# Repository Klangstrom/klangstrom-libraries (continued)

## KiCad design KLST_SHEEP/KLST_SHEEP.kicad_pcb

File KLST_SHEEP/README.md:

# KLANGSTROM / KLST_SHEEP

KLST_SHEEP is a *wolf in sheep's clothing* it is similar to KLST_TINY however comes with a stronger MCU and a screen:

- featuring *KLANGSTROM* library
- programmable in Arduino IDE via USB ( *DFUse Mode* )
- debugging + communication via *virtual USB Serial Port*

## feature list

- STM32H743 MCU with 480MHz, 864KB RAM, 2048KB Flash
- WM8731 audio codec with 2× audio DAC + 2× audio ADC ( 16/24BIT )
- 1× LINE OUT ( stereo )
- 1× LINE IN ( stereo )
- 1× HEADPHONE + MIC ( mono )
- 2× ADC ( 12BIT, opt 6 extra channels )
- 2× DAC ( 12BIT )
- 2× UART ( serial )
- 16× GPIO
- 1× USB Host
- 1× USB Device ( + Power Supply )
- 1× I2C 
- 1× SPI 
- 2× rotary encoders with push buttons
- 16× programmable LEDs with PWM + 1× power LED
- 1× SD card reader
- 1× JTAG/SWD interface + serial debug ( 14-pin )
- programmer + reset + boot flash buttons
- 4× Mounting Holes

## technical details

### timers

| TIMER | FUNCTION                         |
|-------|----------------------------------|
| TIM1  | ENCODER_00                       |
| TIM2  | ENCODER_01                       |
| TIM3  | LED_PWM                          |
| TIM4  | LED_PWM                          |
| TIM5  | (UNUSED)                         |
| TIM6  | BEAT_CALLBACK                    |
| TIM7  | TIMER_SERVO                      |
| TIM8  | LED_PWM                          |
| TIM9  | (nA)                             |
| TIM10 | (nA)                             |
| TIM11 | (nA)                             |
| TIM12 | TIMER_TONE                       |
| TIM13 | LED_PWM                          |
| TIM14 | LED_PWM                          |
| TIM15 | LED_PWM                          |
| TIM16 | LED_PWM                          |
| TIM17 | BUTTON_PRG_IT                    |

#### encoders

timers `TIM1` + `TIM2` are used to handle encoder events.

| FUNCTION          | TIMER:CHANNEL |
|-------------------|---------------|
| ENCODER_00_A+B    | TIM1          |
| ENCODER_00_BUTTON | TIM1:CH3      |
| ENCODER_01_A+B    | TIM2          |
| ENCODER_01_BUTTON | TIM2:CH4      |

#### timers for LEDs with PWM

timers `TIM3` + `TIM4` + `TIM8` + `TIM13` + `TIM14` + `TIM15` + `TIM16` are used for PWM signal generation for LEDs.

| TIMER | CHANNEL |
|-------|---------|
| TIM3  | CH1–4   |
| TIM4  | CH1–4   |
| TIM8  | CH1–4   |
| TIM13 | CH1     |
| TIM14 | CH1     |
| TIM15 | CH1     |
| TIM16 | CH1     |

LEDs are mapped to the following timers:

| LED    | PIN   | TIMER:CHANNEL |
|--------|-------|---------------|
| LED_00 | PB8   | TIM16:CH1     |
| LED_01 | PB5   | TIM3:CH2      |
| LED_02 | PB4   | TIM3:CH1      |
| LED_03 | PC9   | TIM8:CH4      |
| LED_04 | PC8   | TIM8:CH3      |
| LED_05 | PC7*  | TIM8:CH2      |
| LED_06 | PC6*  | TIM8:CH1      |
| LED_07 | PD15  | TIM4:CH4      |
| LED_08 | PD14  | TIM4:CH3      |
| LED_09 | PD13  | TIM4:CH2      |
| LED_10 | PD12  | TIM4:CH1      |
| LED_11 | PB1   | TIM3:CH4      |
| LED_12 | PB0   | TIM3:CH3      |
| LED_13 | PA7   | TIM14:CH1     |
| LED_14 | PA6*  | TIM13:CH1     |
| LED_15 | PA2   | TIM15:CH1     |

#### timer-based PWM alternative PINs

most GPIO pins do not have PWM capabilities. however, the following peripheral pins can be reconfigured to produce PWM signals ( at the expanse of other peripherals ):

| FUNCTION       | PIN  | TIMER:CHANNEL        |
|----------------|------|----------------------|
| DAC_01         | PA5  | TIM2:CH1 / TIM8:CH1N |
| USB_DEVICE-    | PA11 | TIM1:CH4             |
| SPI_DISPLAY_CS | PA15 | TIM2:CH1             |
| I2C_USR_SCL    | PB6  | TIM4:CH1             |
| I2C_USR_SDA    | PB7  | TIM4:CH2             |
| GPIO_10        | PE9  | TIM1:CH1             |
| SPI_USR_CS     | PE11 | TIM1:CH2             |
| SPI_USR_MISO   | PE13 | TIM1:CH3             |
| SPI_USR_MOSI   | PE14 | TIM1:CH4             |

### I2C

| FUNCTION   | PERIPHERAL |
|------------|------------|
| AUDIOCODEC | I2C1       |
| I2C_USR    | I2C2       |

### SPI

| FUNCTION | PERIPHERAL |
|----------|------------|
| SD-CARD  | SPI2       |
| DISPLAY  | SPI3       |
| SPI_USR  | SPI6       |

### UART

| FUNCTION     | PERIPHERAL |
|--------------|------------|
| SERIAL_00    | UART7      |
| SERIAL_01    | UART8      |
| SERIAL_DEBUG | USART2     |

## PIN assignment

| PIN  | LABEL                       |
|------|-----------------------------|
| PC4  | ADC_00                      |
| PC5  | ADC_01                      |
| PB6  | AUDIOCODEC_I2C_SCL          |
| PB7  | AUDIOCODEC_I2C_SDA          |
| PE4  | AUDIOCODEC_SAI1_FS_A        |
| PE2  | AUDIOCODEC_SAI1_MCLK_A      |
| PE5  | AUDIOCODEC_SAI1_SCK_A       |
| PE6  | AUDIOCODEC_SAI1_SD_A        |
| PE3  | AUDIOCODEC_SAI1_SD_B        |
| PB9  | BUTTON_PRG                  |
| PA4  | DAC_00                      |
| PA5  | DAC_01                      |
| PA0  | ENCODER_00_A                |
| PA1  | ENCODER_00_B                |
| PA3  | ENCODER_00_BUTTON           |
| PA8  | ENCODER_01_A                |
| PA9  | ENCODER_01_B                |
| PA10 | ENCODER_01_BUTTON           |
| PD7  | GPIO_00                     |
| PD4  | GPIO_01                     |
| PD3  | GPIO_02                     |
| PD2  | GPIO_03                     |
| PD11 | GPIO_04                     |
| PD10 | GPIO_05                     |
| PD9  | GPIO_06                     |
| PD8  | GPIO_07                     |
| PE15 | GPIO_08                     |
| PE10 | GPIO_09                     |
| PE9  | GPIO_10                     |
| PB2  | GPIO_11                     |
| PC0  | GPIO_12                     |
| PC15 | GPIO_13                     |
| PC14 | GPIO_14                     |
| PC13 | GPIO_15                     |
| PB10 | I2C_USR_SCL                 |
| PB11 | I2C_USR_SDA                 |
| PB8  | LED_00                      |
| PB5  | LED_01                      |
| PB4  | LED_02                      |
| PC9  | LED_03                      |
| PC8  | LED_04                      |
| PC7  | LED_05                      |
| PC6  | LED_06                      |
| PD15 | LED_07                      |
| PD14 | LED_08                      |
| PD13 | LED_09                      |
| PD12 | LED_10                      |
| PB1  | LED_11                      |
| PB0  | LED_12                      |
| PA7  | LED_13                      |
| PA6  | LED_14                      |
| PA2  | LED_15                      |
| PB12 | SDCARD_CS                   |
| PC2  | SDCARD_MISO                 |
| PC3  | SDCARD_MOSI                 |
| PB13 | SDCARD_SCK                  |
| PC1  | SDCARD_CARD_DETECT          |
| PE7  | SERIAL_00_RX                |
| PE8  | SERIAL_00_TX                |
| PE0  | SERIAL_01_RX                |
| PE1  | SERIAL_01_TX                |
| PD6  | SERIAL_DEBUG_RX             |
| PD5  | SERIAL_DEBUG_TX             |
| PA15 | SPI_DISPLAY_CS              |
| PC11 | SPI_DISPLAY_MISO            |
| PC12 | SPI_DISPLAY_MOSI            |
| PD0  | SPI_DISPLAY_REGISTER_SELECT |
| PD1  | SPI_DISPLAY_RESET           |
| PC10 | SPI_DISPLAY_SCK             |
| PE11 | SPI_USR_CS                  |
| PE13 | SPI_USR_MISO                |
| PE14 | SPI_USR_MOSI                |
| PE12 | SPI_USR_SCK                 |
| PA14 | SWD_SWCLK                   |
| PA13 | SWD_SWDIO                   |
| PB3  | SWD_SWO                     |
| PA11 | USB_DEVICE-                 |
| PA12 | USB_DEVICE+                 |
| PB14 | USB_HOST-                   |
| PB15 | USB_HOST+                   |

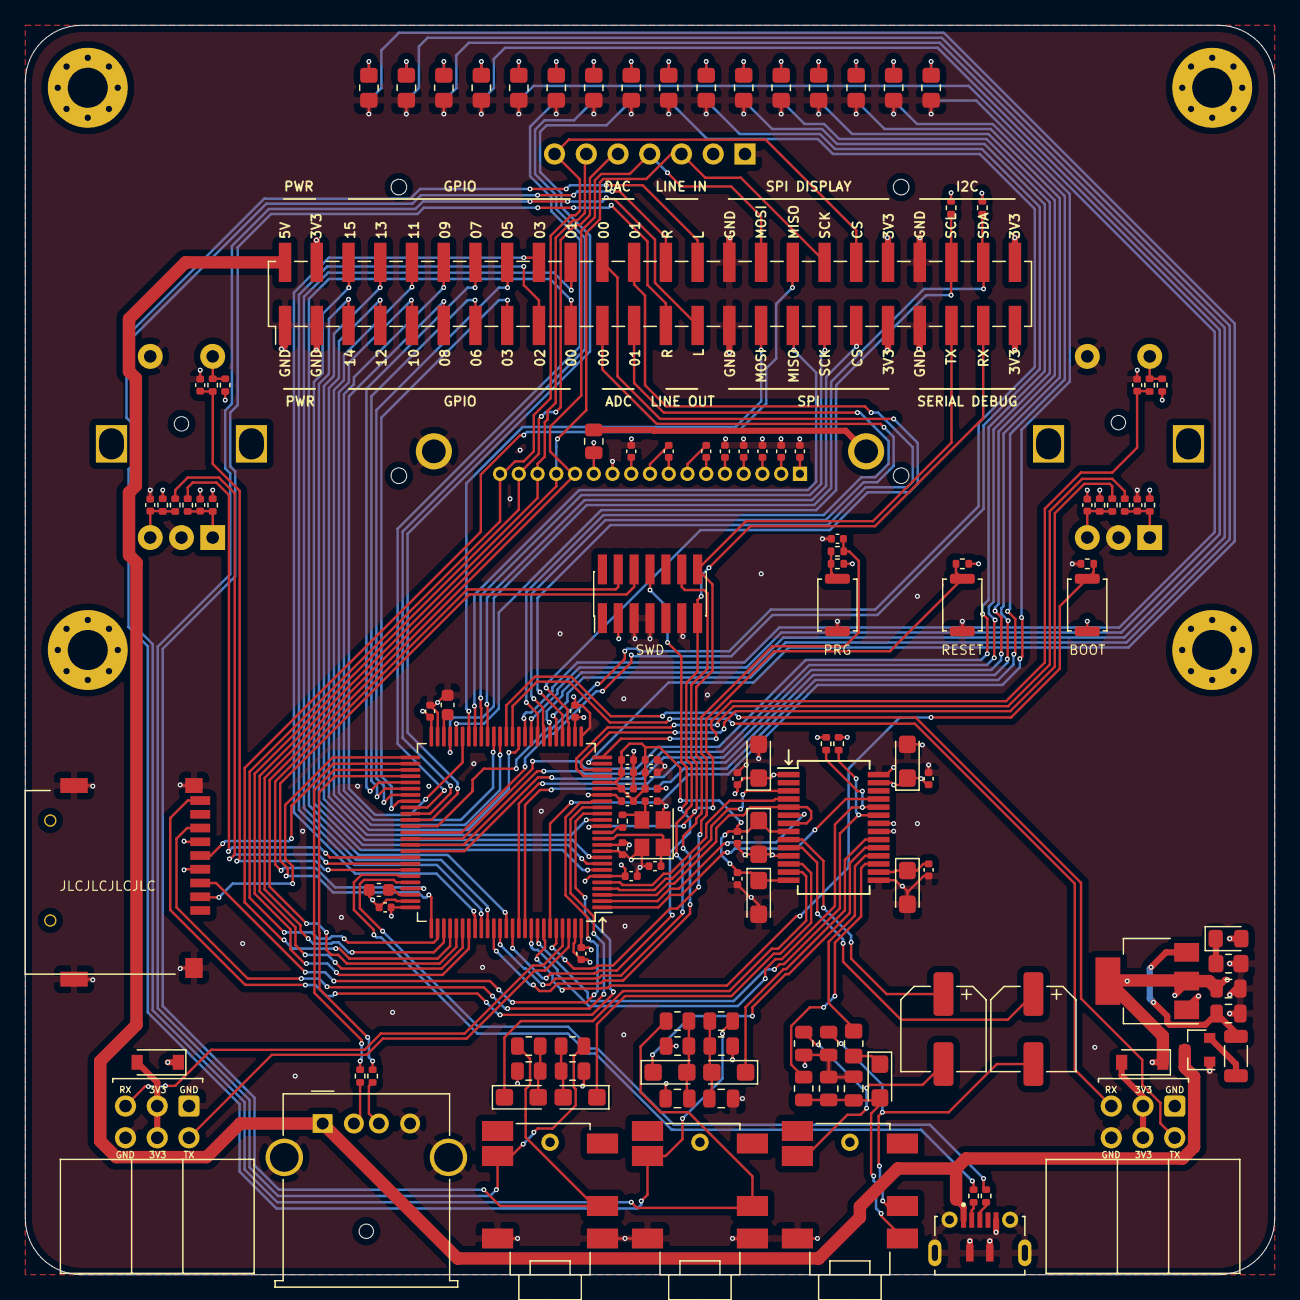
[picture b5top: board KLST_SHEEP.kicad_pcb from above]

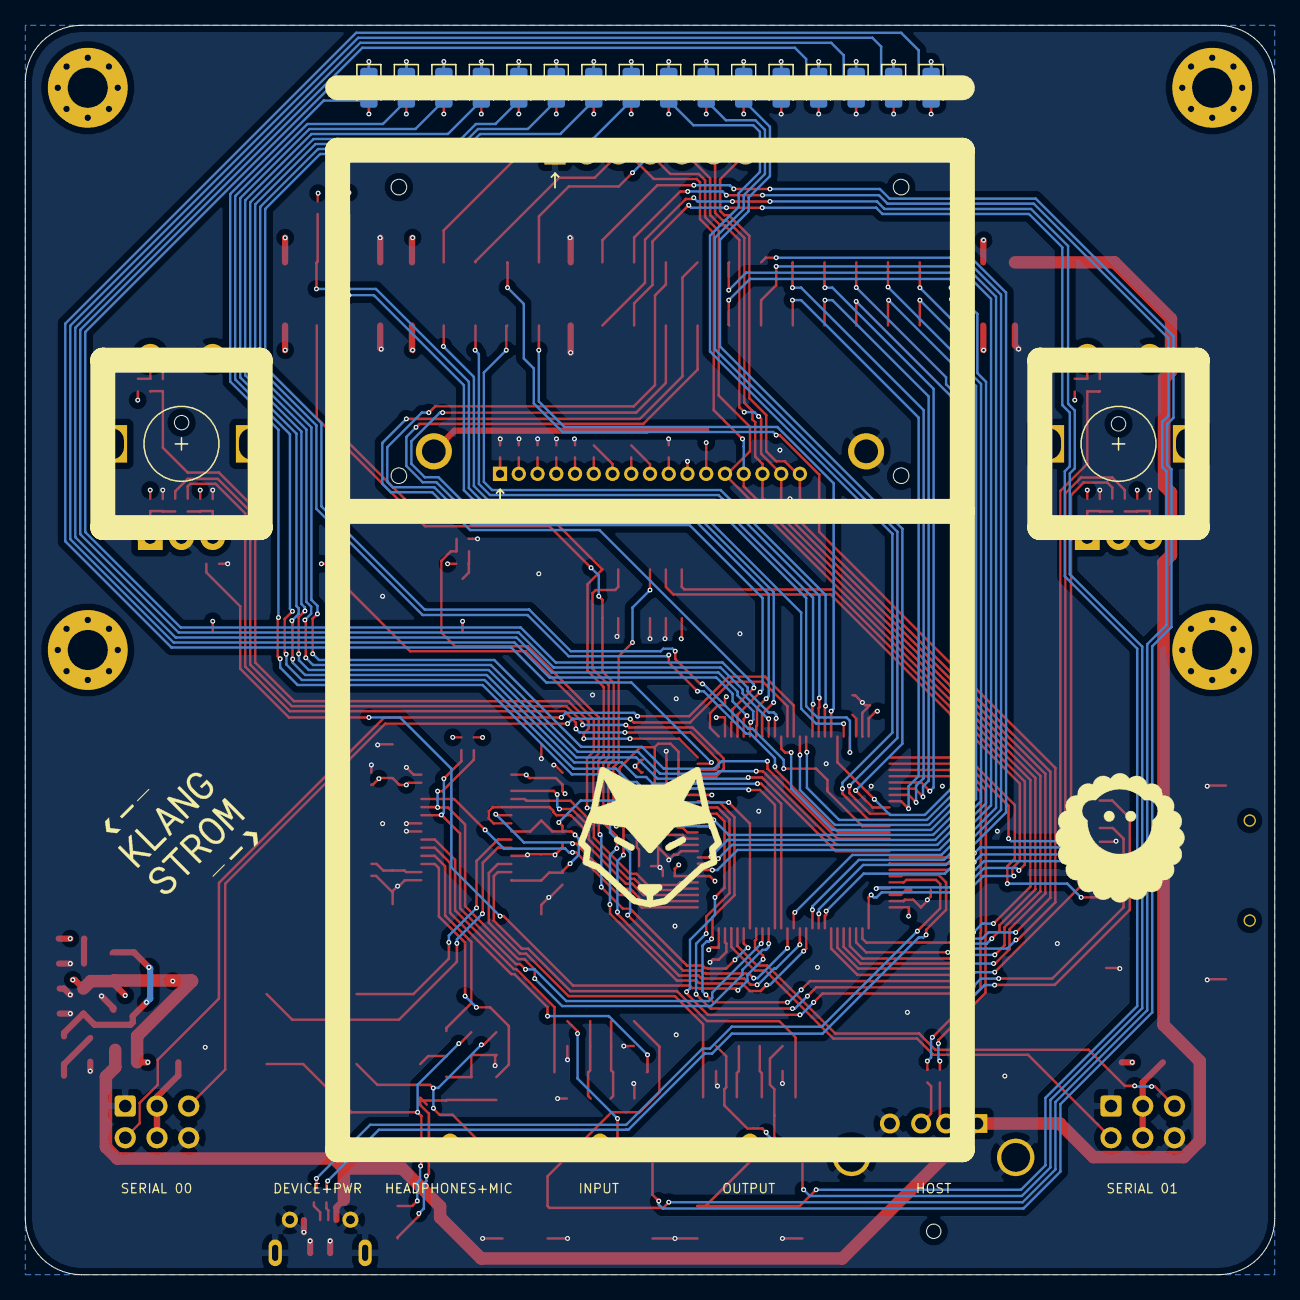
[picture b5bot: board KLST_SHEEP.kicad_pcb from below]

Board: 4 copper layers, 100.0 x 100.0 mm, 159 parts (23 on the bottom side), 155 nets.

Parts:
C1, C2: 12pF; C_0402_1005Metric
C3, C5, C12, C13, C15, C18, C20: 1uF; C_0402_1005Metric
C4, C6, C7, C8, C9, C14, C16, C21, C22, C23, C24, C25, C32, C39, C41, C43, C45, C47, C48, C49, C50, C51, C52, C53: 100nF; C_0402_1005Metric
C10, C11: 10uF; C_0805_2012Metric
C17, C26: 2.2uF; C_0603_1608Metric
C19: 10nF; C_0402_1005Metric
C27, C28: 220uF; CP_Elec_6.3x5.4
C29, C33, C35, C37, C38: 1uF; CP_EIA-3216-18_Kemet-A
C30, C34, C36: 220pF; C_0805_2012Metric
C31, C40, C42, C44, C46: 10uF; CP_EIA-3216-18_Kemet-A
D1, D2, D3, D4, D5, D6, D7, D8, D9, D10, D11, D12, D13, D14, D15, D16, D17: LED; LED_0805_2012Metric_Pad1.15x1.40mm_HandSolder
D18, D19: D_Schottky; D_SOD-123
DS1: NHD-C12832A1Z-FSW-FBW-3V3; Newhaven_Display-NHD-C12832A1Z-FSW-FBW-3V3
FB1: 600Ω@100MHz; L_1206_3216Metric
H1, H2, H3, H4: MountingHole; MountingHole_3.2mm_M3_Pad_Via
J1: Micro_SD_Card_Card_Detect_SPI; microSD_SOFNG_TF-015
J2: PERIPHERALS; PinHeader_2x24_P2.54mm_Vertical_SMD
J3: USB_A; USB_A_Molex_67643_Horizontal
J5: USB_B_Micro; SHOUHAN_MICROXNJ
J8: GMT028-05_V1.1; PinSocket_1x07_P2.54mm_Vertical
J9: ARM_JTAG_SWD(STDC14); PinHeader_2x07_P1.27mm_Vertical_SMD
J10: HEADPHONES+MIC; Korean_Hroparts_Elec_PJ-316A-6A
J11: LINE_IN; Korean_Hroparts_Elec_PJ-316A-6A
J12: LINE_OUT; Korean_Hroparts_Elec_PJ-316A-6A
J13: UART_00; IDC-Header_2x03_P2.54mm_Horizontal
J15: UART_01; IDC-Header_2x03_P2.54mm_Horizontal
L1: 39nH; L_0402_1005Metric
Q1: AO3401A; SOT-23
R1, R2, R3, R4: 22R; R_0402_1005Metric
R5, R6, R7, R8, R9, R10, R11, R12, R13, R16, R17, R18, R19, R20, R21, R22, R23: 1K; R_0805_2012Metric_Pad1.20x1.40mm_HandSolder
R14: 10R; R_0402_1005Metric
R15, R24, R41, R43, R44, R45, R46, R47, R49, R50, R51, R52, R55: 10K; R_0402_1005Metric
R25: 30R; R_0805_2012Metric
R26, R27, R32, R38, R40: 47K; R_0805_2012Metric
R28: 680R; R_0805_2012Metric
R29, R30, R53, R54: 2.2K; R_0402_1005Metric
R31: 330R; R_0805_2012Metric_Pad1.20x1.40mm_HandSolder
R33, R34, R35, R36: 5.6K; R_0805_2012Metric
R37, R39: 100R; R_0805_2012Metric
R42, R48, R56: 1K; R_0402_1005Metric
SW1: BUTTON_BOOT_FLASH; SW_Push_SPST_NO_Alps_SKRK
SW2: BUTTON_RESET; SW_Push_SPST_NO_Alps_SKRK
SW3, SW4: ENCODER; RotaryEncoder_Alps_EC12E-Switch_Vertical_H20mm
SW5: BUTTON; SW_Push_SPST_NO_Alps_SKRK
U1: STM32H743VITx; LQFP-100_14x14mm_P0.5mm
U2: AMS1117-3.3; SOT-223-3_TabPin2
U3: WM8731SEDS; SSOP-28_5.3x10.2mm_P0.65mm
X1: KLST_SHEEP--graphics; KLST--icon
X2: KLST_SHEEP--icon
X3: KLST_SHEEP--wolf
Y1: 16MHz; Crystal_SMD_3225-4Pin_3.2x2.5mm

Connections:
+3.3VA: C13.1, C14.1, C15.1, C16.1, C18.1, C19.1, C39.2, C40.1, C41.2, C42.1, L1.2, U1.20, U1.21, U3.8, U3.14
+3V3: C11.1, C20.1, C21.1, C22.1, C23.1, C24.1, C25.1, C43.2, C44.1, C45.2, C46.1, D9.2, D18.1, D19.1, DS1.12, J1.4, J2.4, J2.39, J2.40, J2.47, J2.48, J8.2, J9.3, L1.1, R15.2, R25.2, R29.1, R30.1, R41.2, R43.1, R44.1, R47.2, R49.1, R50.1, R53.1, R54.1, R55.2, SW1.2, U1.6, U1.11, U1.27, U1.50, U1.75, U1.100, U2.2, U3.1, U3.27
+5V: J2.2, J3.1, J5.1, Q1.3
/ADCDAT: U1.2, U3.6
/ADCLRC: U1.3, U3.5, U3.7
/ADC_00: J2.21, U1.32
/ADC_01: J2.23, U1.33
/AUDIOCODEC_I2C_SCL: R29.2, U1.92, U3.24
/AUDIOCODEC_I2C_SDA: R30.2, U1.93, U3.23
/AUDIOCODEC_I2S_CK: U1.4, U3.3
/AUDIOCODEC_I2S_MCK: U1.1, U3.25
/AUDIOCODEC_I2S_SDO: U1.5, U3.4
/BOOT_FLASH: R24.2, SW1.1, U1.94
/BUTTON_PRG: C53.1, R56.1, U1.96
/DAC_00: J2.22, U1.28
/DAC_01: J2.24, U1.29
/ENCODER_00_A: R45.2, U1.22
/ENCODER_00_B: R46.1, U1.23
/ENCODER_00_BUTTON: C47.1, R42.1, U1.25
/ENCODER_01_A: R51.2, U1.67
/ENCODER_01_B: R52.1, U1.68
/ENCODER_01_BUTTON: C50.1, R48.1, U1.69
/GPIO_00: J2.19, U1.88
/GPIO_01: J2.20, U1.85
/GPIO_02: J2.17, U1.84
/GPIO_03: J2.18, U1.83
/GPIO_04: J2.15, U1.58
/GPIO_05: J2.16, U1.57
/GPIO_06: J2.13, U1.56
/GPIO_07: J2.14, U1.55
/GPIO_08: J2.11, U1.45
/GPIO_09: J2.12, U1.40
/GPIO_10: J2.9, U1.39
/GPIO_11: J2.10, U1.36
/GPIO_12: J2.7, U1.15
/GPIO_13: J2.8, U1.9
/GPIO_14: J2.5, U1.8
/GPIO_15: J2.6, U1.7
/I2C_USR_SCL: J2.44, R54.2, U1.46
/I2C_USR_SDA: J2.46, R53.2, U1.47
/LED_00: D17.2, U1.95
/LED_01: D16.2, U1.91
/LED_02: D15.2, U1.90
/LED_03: D14.2, U1.66
/LED_04: D13.2, U1.65
/LED_05: D12.2, U1.64
/LED_06: D11.2, U1.63
/LED_07: D10.2, U1.62
/LED_08: D8.2, U1.61
/LED_09: D7.2, U1.60
/LED_10: D6.2, U1.59
/LED_11: D5.2, U1.35
/LED_12: D4.2, U1.34
/LED_13: D3.2, U1.31
/LED_14: D2.2, U1.30
/LED_15: D1.2, U1.24
/LINE_IN_LEFT: J2.28, J11.T, R33.2
/LINE_IN_RIGHT: J2.26, J11.R1, R35.2
/LINE_OUT_LEFT: J2.27, J12.T, R37.2
/LINE_OUT_RIGHT: J2.25, J12.R1, R39.2
/RCC_OSC_IN: C1.2, U1.12, Y1.1
/RCC_OSC_OUT: R14.1, U1.13
/SDCARD_CARD_DETECT: J1.9, U1.16
/SDCARD_CS: J1.2, U1.51
/SDCARD_MISO: J1.7, U1.17
/SDCARD_MOSI: J1.3, U1.18
/SDCARD_SCK: J1.5, U1.52
/SERIAL_00_RX: J13.5, U1.37
/SERIAL_00_TX: J13.2, U1.38
/SERIAL_01_RX: J15.5, U1.97
/SERIAL_01_TX: J15.2, U1.98
/SERIAL_DEBUG_RX: J2.45, J9.13, U1.87
/SERIAL_DEBUG_TX: J2.43, J9.14, U1.86
/SPI_DISPLAY_CS: DS1.17, J2.38, J8.7, U1.77
/SPI_DISPLAY_MISO: J2.34, U1.79
/SPI_DISPLAY_MOSI: DS1.13, J2.32, J8.4, U1.80
/SPI_DISPLAY_REGISTER_SELECT: DS1.15, J8.6, U1.81
/SPI_DISPLAY_RESET: DS1.16, J8.5, U1.82
/SPI_DISPLAY_SCK: DS1.14, J2.36, J8.3, U1.78
/SPI_USR_CS: J2.37, U1.41
/SPI_USR_MISO: J2.33, U1.43
/SPI_USR_MOSI: J2.31, U1.44
/SPI_USR_SCK: J2.35, U1.42
/SWD_NRST: J9.12, R15.1, SW2.2, U1.14
/SWD_SWCLK: J9.6, U1.76
/SWD_SWDIO: J9.4, U1.72
/SWD_SWO: J9.8, U1.89
/USB_DEVICE+: R3.1, U1.71
/USB_DEVICE-: R1.1, U1.70
/USB_HOST+: R2.1, U1.54
/USB_HOST-: R4.1, U1.53
/VCAP1: C17.1, U1.48
/VCAP2: C26.1, U1.73
/audio_codec_WM8731/HEADPHONE_LEFT: C27.2, J10.T, R26.1
/audio_codec_WM8731/HEADPHONE_RIGHT: C28.2, J10.R1, R27.1
/audio_codec_WM8731/MIC_IN: C29.2, C30.2, J10.S, R28.1, R32.1
/audio_codec_WM8731/SIGNAL_HEADPHONE_LEFT: C27.1, U3.9
/audio_codec_WM8731/SIGNAL_HEADPHONE_RIGHT: C28.1, U3.10
/audio_codec_WM8731/SIGNAL_IN_LEFT: C33.1, U3.20
/audio_codec_WM8731/SIGNAL_IN_RIGHT: C35.1, U3.19
/audio_codec_WM8731/SIGNAL_MIC_BIAS: R28.2, U3.17
/audio_codec_WM8731/SIGNAL_MIC_IN: R31.2, U3.18
/audio_codec_WM8731/SIGNAL_OUT_LEFT: C37.1, U3.12
/audio_codec_WM8731/SIGNAL_OUT_RIGHT: C38.1, U3.13
GND: C1.1, C2.2, C4.2, C6.2, C7.2, C8.2, C9.2, C10.2, C11.2, C12.2, C13.2, C14.2, C15.2, C16.2, C17.2, C18.2, C19.2, C20.2, C21.2, C22.2, C23.2, C24.2, C25.2, C26.2, C30.1, C31.2, C32.2, C34.1, C36.1, C39.1, C40.2, C41.1, C42.2, C43.1, C44.2, C45.1, C46.2, C47.2, C48.2, C49.2, C50.2, C51.2, C52.2, C53.2, DS1.11, DS1.K, J1.6, J1.10, J2.1, J2.3, J2.29, J2.30, J2.41, J2.42, J3.4, J3.5, J5.5, J5.S, J8.1, J9.5, J9.7, J9.11, J10.R2, J11.R2, J11.S, J12.R2, J12.S, J13.1, J13.6, J15.1, J15.6, Q1.1, R5.1, R6.1, R7.1, R8.1, R9.1, R10.1, R11.1, R12.1, R13.1, R16.1, R17.1, R18.1, R19.1, R20.1, R21.1, R22.1, R23.1, R24.1, R26.2, R27.2, R32.2, R34.2, R36.2, R38.2, R40.2, SW2.1, SW3.C, SW3.S2, SW4.C, SW4.S2, SW5.2, U1.10, U1.19, U1.26, U1.49, U1.74, U1.99, U2.1, U3.11, U3.15, U3.21, U3.22, U3.28, Y1.2, Y1.4
unnamed: C2.1, R14.2, Y1.3
unnamed: C3.1, DS1.8
unnamed: C3.2, DS1.9
unnamed: C4.1, DS1.1
unnamed: C5.1, DS1.7
unnamed: C5.2, DS1.6
unnamed: C6.1, DS1.2
unnamed: C7.1, DS1.3
unnamed: C8.1, DS1.4
unnamed: C9.1, DS1.5
unnamed: C10.1, FB1.1, U2.3
unnamed: C12.1, DS1.10
unnamed: C29.1, R31.1
unnamed: C31.1, C32.1, U3.16
unnamed: C33.2, C34.2, R33.1, R34.1
unnamed: C35.2, C36.2, R35.1, R36.1
unnamed: C37.2, R37.1, R38.1
unnamed: C38.2, R39.1, R40.1
unnamed: C48.1, R44.2, R45.1, SW3.A
unnamed: C49.1, R43.2, R46.2, SW3.B
unnamed: C51.1, R50.2, R51.1, SW4.A
unnamed: C52.1, R49.2, R52.2, SW4.B
unnamed: D1.1, R5.2
unnamed: D2.1, R6.2
unnamed: D3.1, R7.2
unnamed: D4.1, R8.2
unnamed: D5.1, R9.2
unnamed: D6.1, R10.2
unnamed: D7.1, R11.2
unnamed: D8.1, R12.2
unnamed: D9.1, R13.2
unnamed: D10.1, R16.2
unnamed: D11.1, R17.2
unnamed: D12.1, R18.2
unnamed: D13.1, R19.2
unnamed: D14.1, R20.2
unnamed: D15.1, R21.2
unnamed: D16.1, R22.2
unnamed: D17.1, R23.2
unnamed: D18.2, J13.3, J13.4
unnamed: D19.2, J15.3, J15.4
unnamed: DS1.A, R25.1
unnamed: FB1.2, Q1.2
unnamed: J3.2, R4.2
unnamed: J3.3, R2.2
unnamed: J5.2, R1.2
unnamed: J5.3, R3.2
unnamed: R41.1, R42.2, SW3.S1
unnamed: R47.1, R48.2, SW4.S1
unnamed: R55.1, R56.2, SW5.1

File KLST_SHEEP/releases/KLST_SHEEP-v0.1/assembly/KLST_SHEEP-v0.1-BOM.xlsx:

Comment | Designator | Footprint | JLCPCB Part #
Micro_SD_Card_Card_Detect_SPI | J1 | Connector_Card:microSD_SOFNG_TF-015 | C113206
STM32H743VITx | U1 | Package_QFP:LQFP-100_14x14mm_P0.5mm | C114409
BUTTON_RESET | SW2 | Button_Switch_SMD:SW_Push_SPST_NO_Alps_SKRK | C115357
BUTTON_BOOT_FLASH | SW1 | Button_Switch_SMD:SW_Push_SPST_NO_Alps_SKRK | C115357
BUTTON | SW5 | Button_Switch_SMD:SW_Push_SPST_NO_Alps_SKRK | C115357
1K | R56 | Resistor_SMD:R_0402_1005Metric | C11702
1K | R42 | Resistor_SMD:R_0402_1005Metric | C11702
1K | R48 | Resistor_SMD:R_0402_1005Metric | C11702
HEADPHONES+MIC | J10 | KLST_SHEEP:Korean_Hroparts_Elec_PJ-316A-6A | C128987
LINE_IN | J11 | KLST_SHEEP:Korean_Hroparts_Elec_PJ-316A-6A | C128987
LINE_OUT | J12 | KLST_SHEEP:Korean_Hroparts_Elec_PJ-316A-6A | C128987
16MHz | Y1 | Crystal:Crystal_SMD_3225-4Pin_3.2x2.5mm | C13738
UART_01 | J15 | Connector_IDC:IDC-Header_2x03_P2.54mm_Horizontal | C146629
UART_00 | J13 | Connector_IDC:IDC-Header_2x03_P2.54mm_Horizontal | C146629
AO3401A | Q1 | Package_TO_SOT_SMD:SOT-23 | C15127
10nF | C19 | Capacitor_SMD:C_0402_1005Metric | C15195
100nF | C14 | Capacitor_SMD:C_0402_1005Metric | C1525
100nF | C21 | Capacitor_SMD:C_0402_1005Metric | C1525
100nF | C22 | Capacitor_SMD:C_0402_1005Metric | C1525
100nF | C23 | Capacitor_SMD:C_0402_1005Metric | C1525
100nF | C24 | Capacitor_SMD:C_0402_1005Metric | C1525
100nF | C25 | Capacitor_SMD:C_0402_1005Metric | C1525
100nF | C16 | Capacitor_SMD:C_0402_1005Metric | C1525
100nF | C4 | Capacitor_SMD:C_0402_1005Metric | C1525
100nF | C6 | Capacitor_SMD:C_0402_1005Metric | C1525
100nF | C7 | Capacitor_SMD:C_0402_1005Metric | C1525
100nF | C8 | Capacitor_SMD:C_0402_1005Metric | C1525
100nF | C9 | Capacitor_SMD:C_0402_1005Metric | C1525
100nF | C32 | Capacitor_SMD:C_0402_1005Metric | C1525
100nF | C43 | Capacitor_SMD:C_0402_1005Metric | C1525
100nF | C45 | Capacitor_SMD:C_0402_1005Metric | C1525
100nF | C39 | Capacitor_SMD:C_0402_1005Metric | C1525
100nF | C41 | Capacitor_SMD:C_0402_1005Metric | C1525
100nF | C53 | Capacitor_SMD:C_0402_1005Metric | C1525
100nF | C48 | Capacitor_SMD:C_0402_1005Metric | C1525
100nF | C49 | Capacitor_SMD:C_0402_1005Metric | C1525
100nF | C47 | Capacitor_SMD:C_0402_1005Metric | C1525
100nF | C51 | Capacitor_SMD:C_0402_1005Metric | C1525
100nF | C52 | Capacitor_SMD:C_0402_1005Metric | C1525
100nF | C50 | Capacitor_SMD:C_0402_1005Metric | C1525
12pF | C1 | Capacitor_SMD:C_0402_1005Metric | C1547
12pF | C2 | Capacitor_SMD:C_0402_1005Metric | C1547
10uF | C10 | Capacitor_SMD:C_0805_2012Metric | C15850
10uF | C11 | Capacitor_SMD:C_0805_2012Metric | C15850
100R | R37 | Resistor_SMD:R_0805_2012Metric | C17408
100R | R39 | Resistor_SMD:R_0805_2012Metric | C17408
1K | R13 | Resistor_SMD:R_0805_2012Metric_Pad1.20x1.40mm_HandSolder | C17513
1K | R6 | Resistor_SMD:R_0805_2012Metric_Pad1.20x1.40mm_HandSolder | C17513
1K | R7 | Resistor_SMD:R_0805_2012Metric_Pad1.20x1.40mm_HandSolder | C17513
1K | R5 | Resistor_SMD:R_0805_2012Metric_Pad1.20x1.40mm_HandSolder | C17513
1K | R8 | Resistor_SMD:R_0805_2012Metric_Pad1.20x1.40mm_HandSolder | C17513
1K | R9 | Resistor_SMD:R_0805_2012Metric_Pad1.20x1.40mm_HandSolder | C17513
1K | R10 | Resistor_SMD:R_0805_2012Metric_Pad1.20x1.40mm_HandSolder | C17513
1K | R11 | Resistor_SMD:R_0805_2012Metric_Pad1.20x1.40mm_HandSolder | C17513
1K | R12 | Resistor_SMD:R_0805_2012Metric_Pad1.20x1.40mm_HandSolder | C17513
1K | R17 | Resistor_SMD:R_0805_2012Metric_Pad1.20x1.40mm_HandSolder | C17513
1K | R18 | Resistor_SMD:R_0805_2012Metric_Pad1.20x1.40mm_HandSolder | C17513
1K | R16 | Resistor_SMD:R_0805_2012Metric_Pad1.20x1.40mm_HandSolder | C17513
1K | R19 | Resistor_SMD:R_0805_2012Metric_Pad1.20x1.40mm_HandSolder | C17513
1K | R20 | Resistor_SMD:R_0805_2012Metric_Pad1.20x1.40mm_HandSolder | C17513
1K | R21 | Resistor_SMD:R_0805_2012Metric_Pad1.20x1.40mm_HandSolder | C17513
1K | R22 | Resistor_SMD:R_0805_2012Metric_Pad1.20x1.40mm_HandSolder | C17513
1K | R23 | Resistor_SMD:R_0805_2012Metric_Pad1.20x1.40mm_HandSolder | C17513
330R | R31 | Resistor_SMD:R_0805_2012Metric_Pad1.20x1.40mm_HandSolder | C17630
30R | R25 | Resistor_SMD:R_0805_2012Metric | C17634
47K | R26 | Resistor_SMD:R_0805_2012Metric | C17713
47K | R27 | Resistor_SMD:R_0805_2012Metric | C17713
47K | R38 | Resistor_SMD:R_0805_2012Metric | C17713
47K | R40 | Resistor_SMD:R_0805_2012Metric | C17713
47K | R32 | Resistor_SMD:R_0805_2012Metric | C17713
680R | R28 | Resistor_SMD:R_0805_2012Metric | C17798
2.2uF | C26 | Capacitor_SMD:C_0603_1608Metric | C23630
2.2uF | C17 | Capacitor_SMD:C_0603_1608Metric | C23630
10R | R14 | Resistor_SMD:R_0402_1005Metric | C25077
22R | R2 | Resistor_SMD:R_0402_1005Metric | C25092
22R | R4 | Resistor_SMD:R_0402_1005Metric | C25092
22R | R1 | Resistor_SMD:R_0402_1005Metric | C25092
22R | R3 | Resistor_SMD:R_0402_1005Metric | C25092
10K | R15 | Resistor_SMD:R_0402_1005Metric | C25744
10K | R24 | Resistor_SMD:R_0402_1005Metric | C25744
10K | R55 | Resistor_SMD:R_0402_1005Metric | C25744
10K | R45 | Resistor_SMD:R_0402_1005Metric | C25744
10K | R46 | Resistor_SMD:R_0402_1005Metric | C25744
10K | R43 | Resistor_SMD:R_0402_1005Metric | C25744
10K | R44 | Resistor_SMD:R_0402_1005Metric | C25744
10K | R41 | Resistor_SMD:R_0402_1005Metric | C25744
10K | R51 | Resistor_SMD:R_0402_1005Metric | C25744
10K | R52 | Resistor_SMD:R_0402_1005Metric | C25744
10K | R49 | Resistor_SMD:R_0402_1005Metric | C25744
10K | R50 | Resistor_SMD:R_0402_1005Metric | C25744
10K | R47 | Resistor_SMD:R_0402_1005Metric | C25744
2.2K | R53 | Resistor_SMD:R_0402_1005Metric | C25879
2.2K | R54 | Resistor_SMD:R_0402_1005Metric | C25879
2.2K | R30 | Resistor_SMD:R_0402_1005Metric | C25879
2.2K | R29 | Resistor_SMD:R_0402_1005Metric | C25879
39nH | L1 | Inductor_SMD:L_0402_1005Metric | C26443
220uF | C27 | Capacitor_SMD:CP_Elec_6.3x5.4 | C3345
220uF | C28 | Capacitor_SMD:CP_Elec_6.3x5.4 | C3345
LED | D9 | LED_SMD:LED_0805_2012Metric_Pad1.15x1.40mm_HandSolder | C34499
USB_B_Micro | J5 | KLST_SHEEP:SHOUHAN_MICROXNJ | C404969
5.6K | R33 | Resistor_SMD:R_0805_2012Metric | C4382
5.6K | R34 | Resistor_SMD:R_0805_2012Metric | C4382
5.6K | R35 | Resistor_SMD:R_0805_2012Metric | C4382
5.6K | R36 | Resistor_SMD:R_0805_2012Metric | C4382
USB_A | J3 | Connector_USB:USB_A_Molex_67643_Horizontal | C456018
1uF | C13 | Capacitor_SMD:C_0402_1005Metric | C52923
1uF | C20 | Capacitor_SMD:C_0402_1005Metric | C52923
1uF | C18 | Capacitor_SMD:C_0402_1005Metric | C52923
1uF | C15 | Capacitor_SMD:C_0402_1005Metric | C52923
1uF | C3 | Capacitor_SMD:C_0402_1005Metric | C52923
1uF | C5 | Capacitor_SMD:C_0402_1005Metric | C52923
1uF | C12 | Capacitor_SMD:C_0402_1005Metric | C52923
220pF | C34 | Capacitor_SMD:C_0805_2012Metric | C53172
220pF | C36 | Capacitor_SMD:C_0805_2012Metric | C53172
220pF | C30 | Capacitor_SMD:C_0805_2012Metric | C53172
AMS1117-3.3 | U2 | Package_TO_SOT_SMD:SOT-223-3_TabPin2 | C6186
10uF | C31 | Capacitor_Tantalum_SMD:CP_EIA-3216-18_Kemet-A | C7171
10uF | C44 | Capacitor_Tantalum_SMD:CP_EIA-3216-18_Kemet-A | C7171
10uF | C46 | Capacitor_Tantalum_SMD:CP_EIA-3216-18_Kemet-A | C7171
10uF | C40 | Capacitor_Tantalum_SMD:CP_EIA-3216-18_Kemet-A | C7171
10uF | C42 | Capacitor_Tantalum_SMD:CP_EIA-3216-18_Kemet-A | C7171
1uF | C33 | Capacitor_Tantalum_SMD:CP_EIA-3216-18_Kemet-A | C7175
1uF | C35 | Capacitor_Tantalum_SMD:CP_EIA-3216-18_Kemet-A | C7175
1uF | C37 | Capacitor_Tantalum_SMD:CP_EIA-3216-18_Kemet-A | C7175
1uF | C38 | Capacitor_Tantalum_SMD:CP_EIA-3216-18_Kemet-A | C7175
1uF | C29 | Capacitor_Tantalum_SMD:CP_EIA-3216-18_Kemet-A | C7175
600Ω@100MHz | FB1 | Inductor_SMD:L_1206_3216Metric | C73732
D_Schottky | D18 | Diode_SMD:D_SOD-123 | C8598
D_Schottky | D19 | Diode_SMD:D_SOD-123 | C8598

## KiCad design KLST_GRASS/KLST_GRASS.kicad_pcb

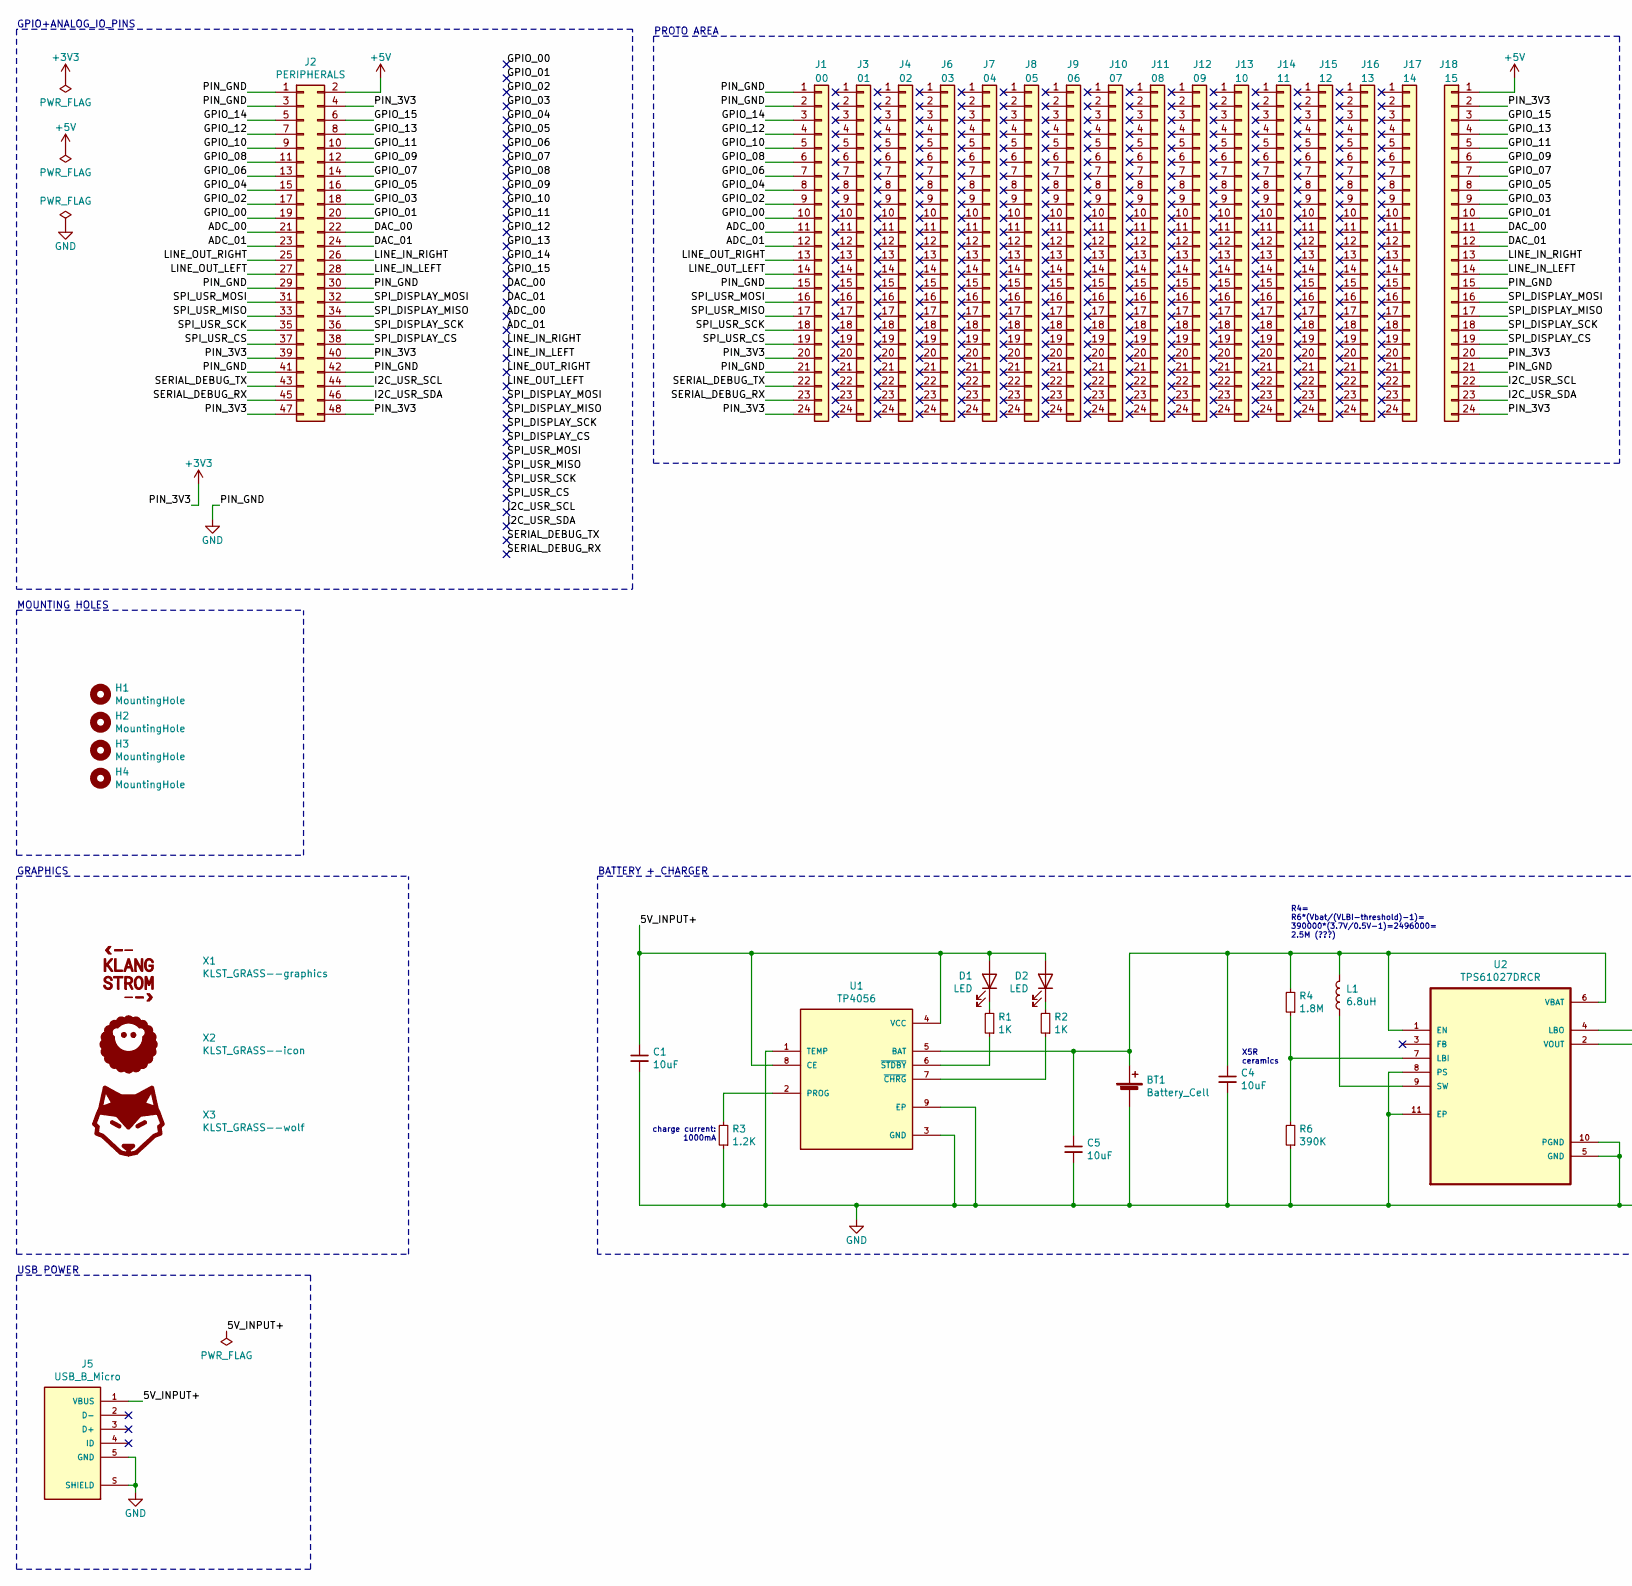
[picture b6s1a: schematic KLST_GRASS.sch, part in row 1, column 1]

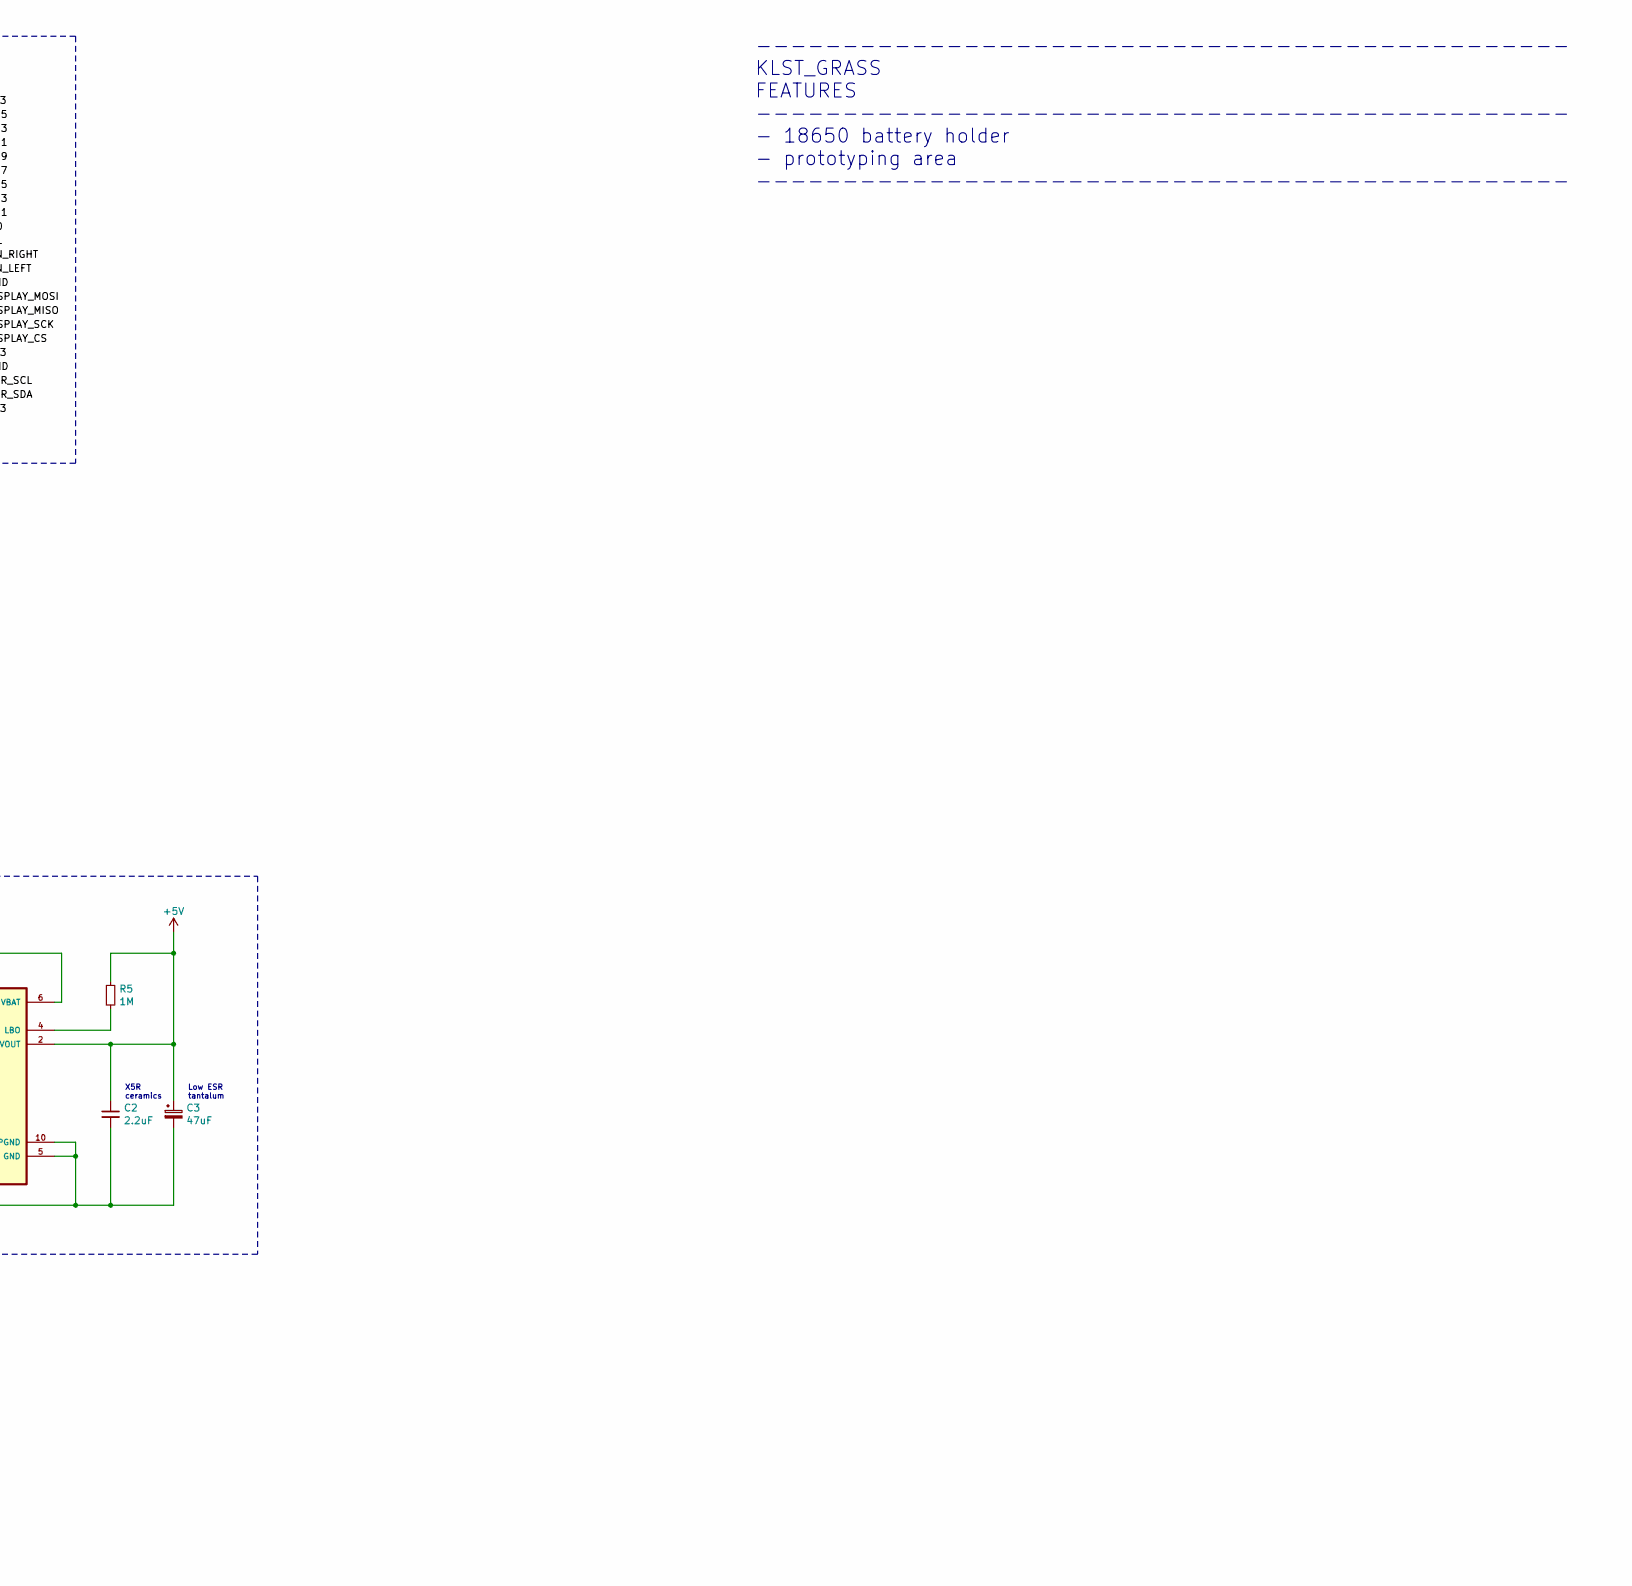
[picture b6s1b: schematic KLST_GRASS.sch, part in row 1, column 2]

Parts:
BT1: Battery_Cell; Keystone Electronics - PC Battery Clip #54
C1, C4, C5: 10uF; C_0603_1608Metric_Pad1.08x0.95mm_HandSolder; MFR.Part # CL10A106MA8NRNC; JLCPCB Part # C96446
C2: 2.2uF; C_0603_1608Metric_Pad1.08x0.95mm_HandSolder; MFR.Part # CL10A225KO8NNNC; JLCPCB Part # C23630
C3: 47uF; CP_EIA-3216-18_Kemet-A_Pad1.58x1.35mm_HandSolder; MFR.Part # TC212A476K006A; JLCPCB Part # C112111
D1, D2: LED; LED_0805_2012Metric_Pad1.15x1.40mm_HandSolder; MFR.Part # C34499; JLCPCB Part # C34499
H1, H2, H3, H4: MountingHole; MountingHole_3.2mm_M3_Pad_Via; MFR.Part # DNF; JLCPCB Part # DNF
J1: 00; PinHeader_1x24_P2.54mm_Vertical
J2: PERIPHERALS; PinHeader_2x24_P2.54mm_Vertical; MFR.Part # DNF; JLCPCB Part # DNF
J3: 01; PinHeader_1x24_P2.54mm_Vertical
J4: 02; PinHeader_1x24_P2.54mm_Vertical
J5: USB_B_Micro; SHOUHAN_MICROXNJ; MFR.Part # MicroXNJ; JLCPCB Part # C404969
J6: 03; PinHeader_1x24_P2.54mm_Vertical
J7: 04; PinHeader_1x24_P2.54mm_Vertical
J8: 05; PinHeader_1x24_P2.54mm_Vertical
J9: 06; PinHeader_1x24_P2.54mm_Vertical
J10: 07; PinHeader_1x24_P2.54mm_Vertical
J11: 08; PinHeader_1x24_P2.54mm_Vertical
J12: 09; PinHeader_1x24_P2.54mm_Vertical
J13: 10; PinHeader_1x24_P2.54mm_Vertical
J14: 11; PinHeader_1x24_P2.54mm_Vertical
J15: 12; PinHeader_1x24_P2.54mm_Vertical
J16: 13; PinHeader_1x24_P2.54mm_Vertical
J17: 14; PinHeader_1x24_P2.54mm_Vertical
J18: 15; PinHeader_1x24_P2.54mm_Vertical
L1: 6.8uH; L_Bourns-SRN4018; MFR.Part # PRS4018-6R8MT; JLCPCB Part # C105667
R1, R2: 1K; R_0805_2012Metric_Pad1.20x1.40mm_HandSolder; MFR.Part # 0805W8F1001T5E; JLCPCB Part # C17513
R3: 1.2K; R_0805_2012Metric_Pad1.20x1.40mm_HandSolder; MFR.Part # 0805W8F1201T5E; JLCPCB Part # C17379
R4: 1.8M; R_0805_2012Metric_Pad1.20x1.40mm_HandSolder; MFR.Part # 0805W8F1804T5E; JLCPCB Part # C17399
R5: 1M; R_0805_2012Metric_Pad1.20x1.40mm_HandSolder; MFR.Part # 0805W8F1004T5E; JLCPCB Part # C17514
R6: 390K; R_0805_2012Metric_Pad1.20x1.40mm_HandSolder; MFR.Part # 0805W8F3903T5E; JLCPCB Part # C17656
U1: TP4056; SOP127P600X175-9N; MFR.Part # TP4056-42-ESOP8; JLCPCB Part # C16581
U2: TPS61027DRCR; MFR.Part # TPS61027DRCR; JLCPCB Part # C80258
X1: KLST_GRASS--graphics; KLST--icon; MFR.Part # DNF; JLCPCB Part # DNF
X2: KLST_GRASS--icon; MFR.Part # DNF; JLCPCB Part # DNF
X3: KLST_GRASS--wolf; MFR.Part # DNF; JLCPCB Part # DNF

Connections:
+3V3: J1.20, J1.24, J2.4, J2.39, J2.40, J2.47, J2.48, J18.2, J18.20, J18.24
+5V: C2.1, C3.1, J2.2, J18.1, R5.1, U2.2 (VOUT)
/5V_INPUT+: C1.1, D1.2 (A), D2.2 (A), J5.1 (VBUS), U1.4 (VCC), U1.8 (CE)
/ADC_00: J1.11, J2.21
/ADC_01: J1.12, J2.23
/DAC_00: J2.22, J18.11
/DAC_01: J2.24, J18.12
/GPIO_00: J1.10, J2.19
/GPIO_01: J2.20, J18.10
/GPIO_02: J1.9, J2.17
/GPIO_03: J2.18, J18.9
/GPIO_04: J1.8, J2.15
/GPIO_05: J2.16, J18.8
/GPIO_06: J1.7, J2.13
/GPIO_07: J2.14, J18.7
/GPIO_08: J1.6, J2.11
/GPIO_09: J2.12, J18.6
/GPIO_10: J1.5, J2.9
/GPIO_11: J2.10, J18.5
/GPIO_12: J1.4, J2.7
/GPIO_13: J2.8, J18.4
/GPIO_14: J1.3, J2.5
/GPIO_15: J2.6, J18.3
/I2C_USR_SCL: J2.44, J18.22
/I2C_USR_SDA: J2.46, J18.23
/LINE_IN_LEFT: J2.28, J18.14
/LINE_IN_RIGHT: J2.26, J18.13
/LINE_OUT_LEFT: J1.14, J2.27
/LINE_OUT_RIGHT: J1.13, J2.25
/SERIAL_DEBUG_RX: J1.23, J2.45
/SERIAL_DEBUG_TX: J1.22, J2.43
/SPI_DISPLAY_CS: J2.38, J18.19
/SPI_DISPLAY_MISO: J2.34, J18.17
/SPI_DISPLAY_MOSI: J2.32, J18.16
/SPI_DISPLAY_SCK: J2.36, J18.18
/SPI_USR_CS: J1.19, J2.37
/SPI_USR_MISO: J1.17, J2.33
/SPI_USR_MOSI: J1.16, J2.31
/SPI_USR_SCK: J1.18, J2.35
GND: BT1.2 (-), C1.2, C2.2, C3.2, C4.2, C5.2, J1.1, J1.2, J1.15, J1.21, J2.1, J2.3, J2.29, J2.30, J2.41, J2.42, J5.5 (GND), J5.S (SHIELD), J18.15, J18.21, R3.1, R6.1, U1.1 (TEMP), U1.3 (GND), U1.9 (EP), U2.5 (GND), U2.8 (PS), U2.10 (PGND), U2.11 (EP)
unnamed: BT1.1 (+), C4.1, C5.1, L1.2, R4.2, U1.5 (BAT), U2.1 (EN), U2.6 (VBAT)
unnamed: D1.1 (K), R1.2
unnamed: D2.1 (K), R2.2
unnamed: L1.1, U2.9 (SW)
unnamed: R1.1, U1.6 (~STDBY)
unnamed: R2.1, U1.7 (~CHRG)
unnamed: R3.2, U1.2 (PROG)
unnamed: R4.1, R6.2, U2.7 (LBI)
unnamed: R5.2, U2.4 (LBO)

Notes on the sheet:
GRAPHICS
----------------------------------------------- KLST_GRASS FEATURES ----------------------------------------------- - 18650 battery holder - prototyping area -----------------------------------------------
GPIO+ANALOG_IO_PINS
MOUNTING HOLES
charge current: 1000mA
R4= R6*(Vbat/(VLBI-threshold)-1)= 390000*(3.7V/0.5V-1)=2496000= 2.5M (???)
X5R ceramics
Low ESR tantalum
BATTERY + CHARGER
USB POWER
PROTO AREA

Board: 2 copper layers, 42 parts (1 on the bottom side), 49 nets, no tracks yet.
